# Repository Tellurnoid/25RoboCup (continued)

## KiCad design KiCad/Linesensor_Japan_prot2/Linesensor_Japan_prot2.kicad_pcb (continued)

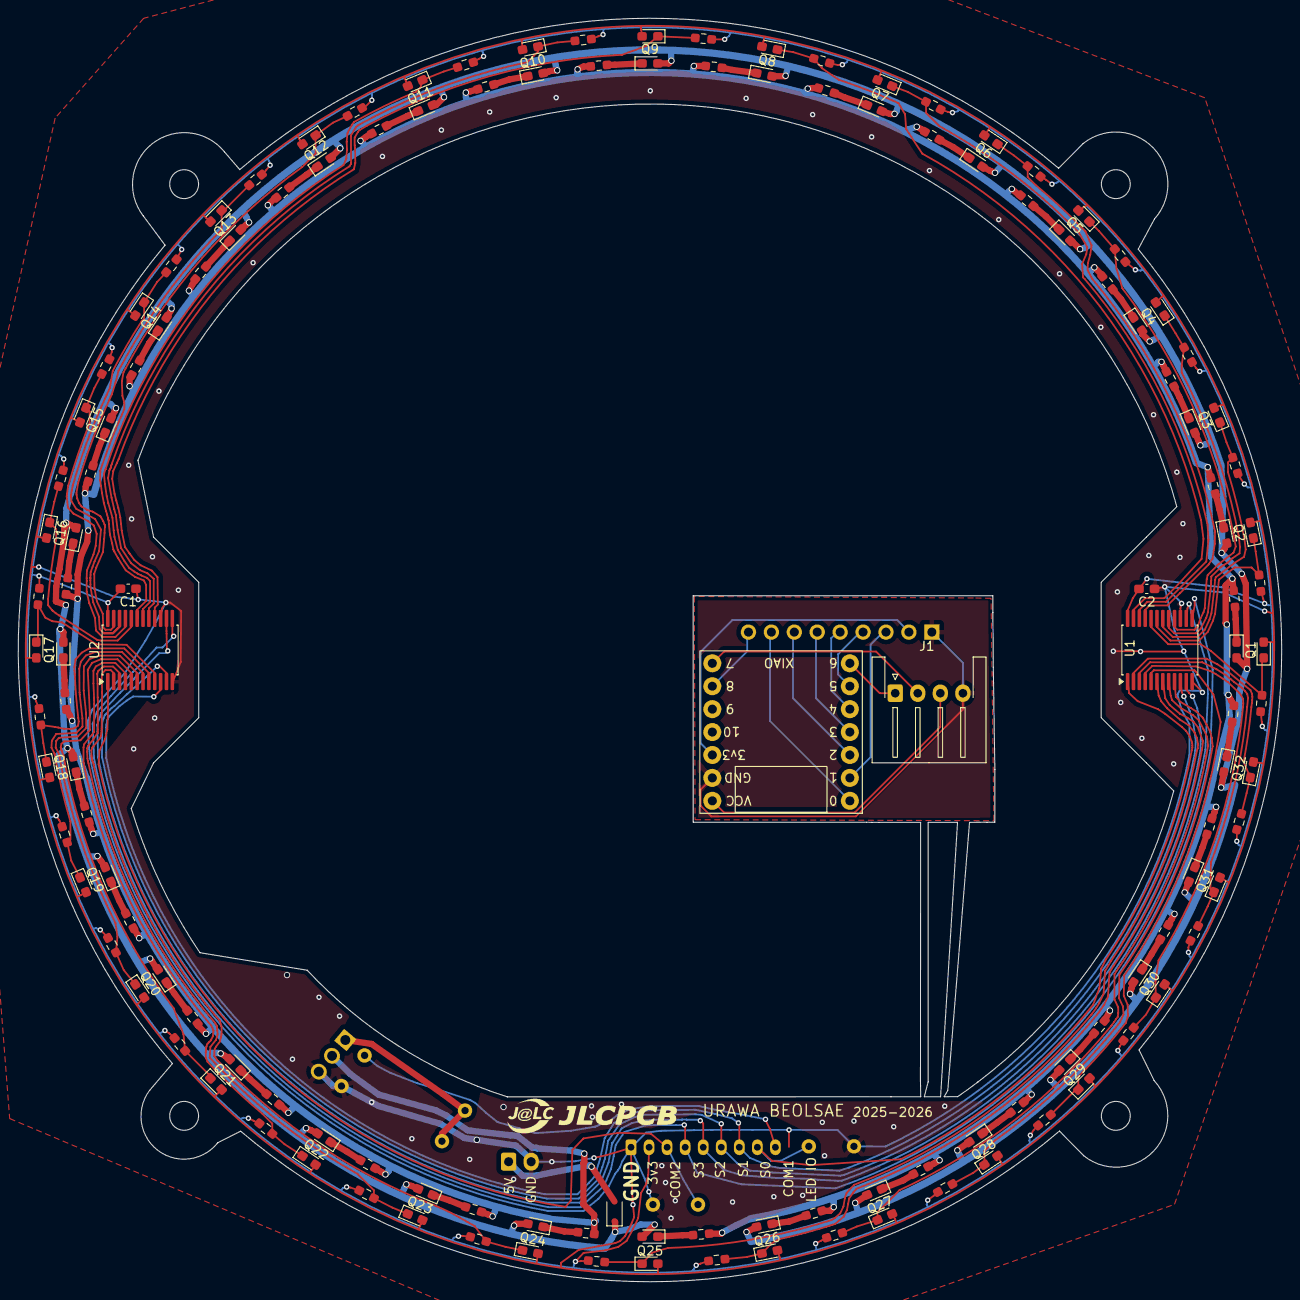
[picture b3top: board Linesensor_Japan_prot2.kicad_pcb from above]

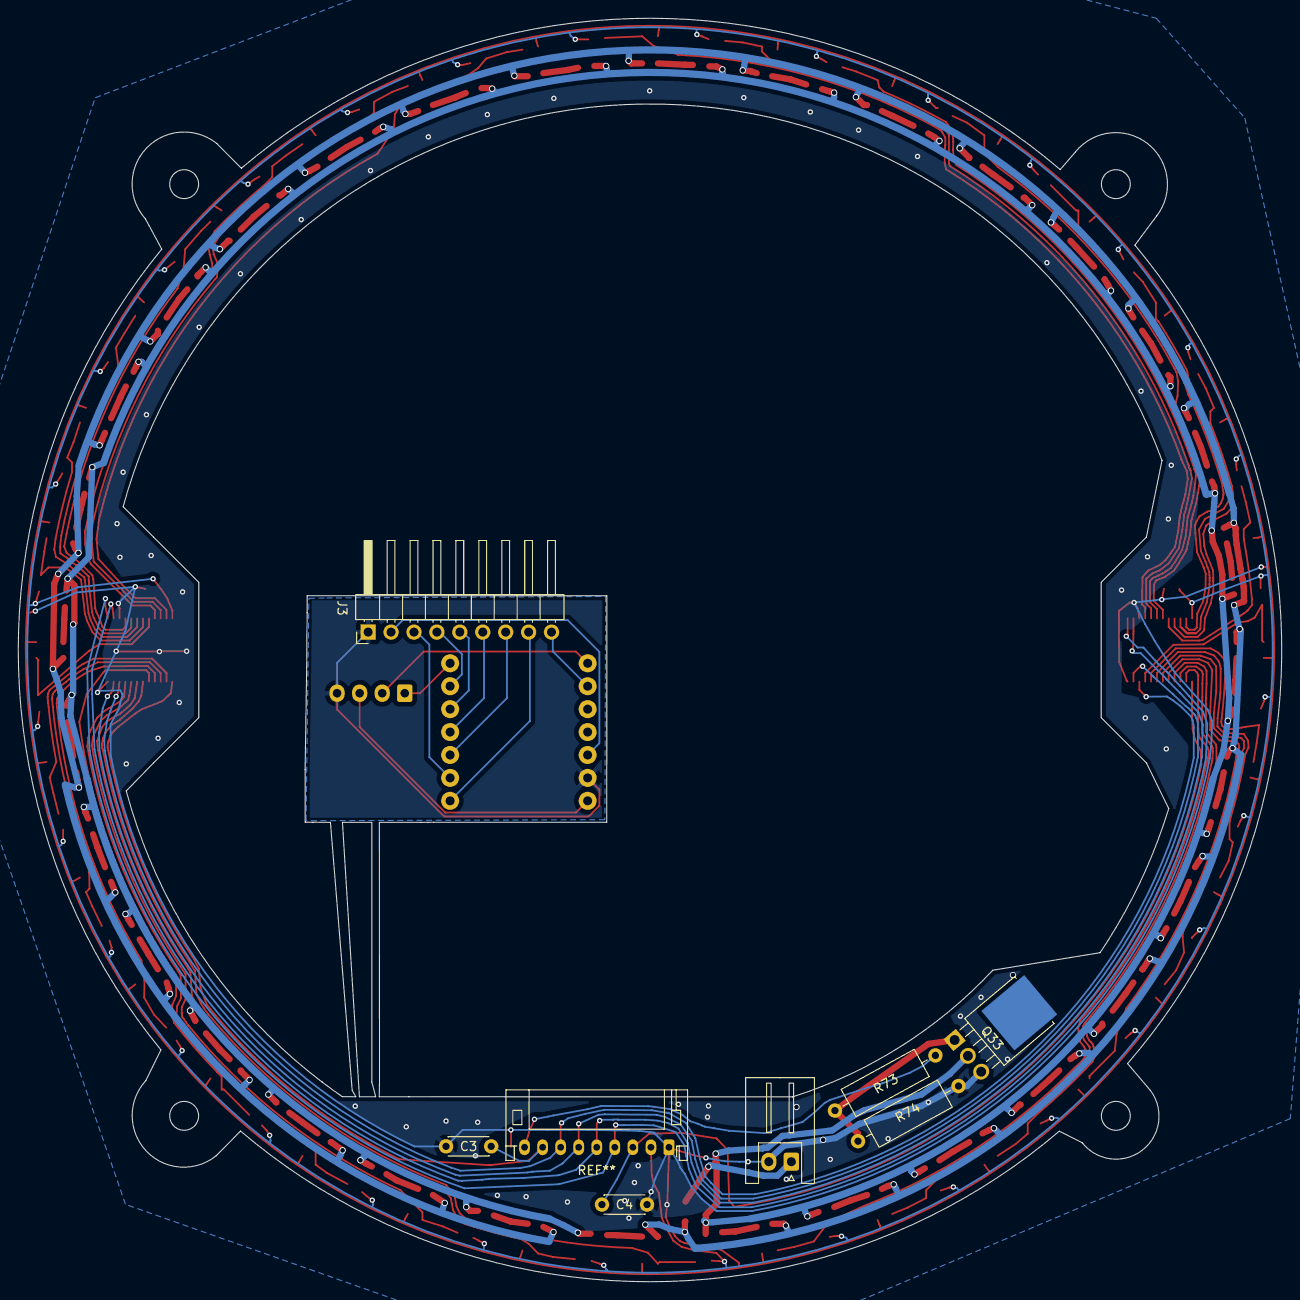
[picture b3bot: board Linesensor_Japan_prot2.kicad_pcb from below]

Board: 2 copper layers, 140.0 x 140.0 mm, 145 parts (7 on the bottom side), 79 nets.

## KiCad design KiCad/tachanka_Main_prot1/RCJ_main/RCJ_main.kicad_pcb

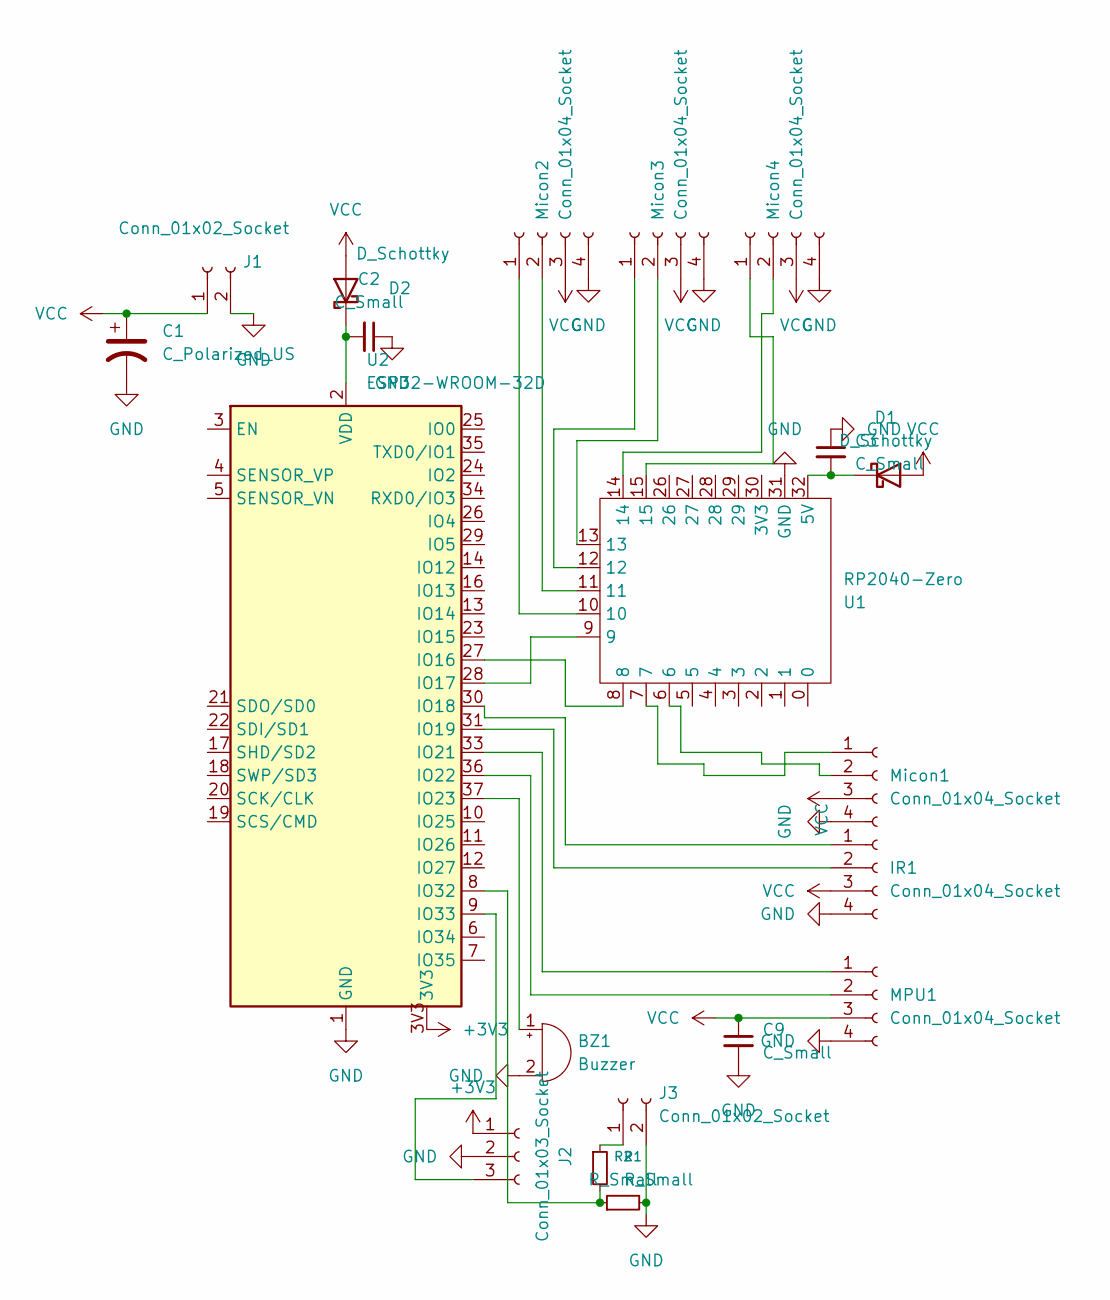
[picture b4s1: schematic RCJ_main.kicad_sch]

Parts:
BZ1: Buzzer; Buzzer_12x9.5RM7.6
C1: C_Polarized_US; CP_Radial_D8.0mm_P3.50mm
C2, C3, C9: C_Small; CP_EIA-1608-08_AVX-J_HandSolder
D1, D2: D_Schottky; D_SOD-123
IR1: Conn_01x04_Socket; JST_PH_S4B-PH-K_1x04_P2.00mm_Horizontal
J1: Conn_01x02_Socket; JST_XH_S2B-XH-A-1_1x02_P2.50mm_Horizontal
J2: Conn_01x03_Socket; JST_PH_B3B-PH-K_1x03_P2.00mm_Vertical
J3: Conn_01x02_Socket; JST_PH_B2B-PH-K_1x02_P2.00mm_Vertical
MPU1: Conn_01x04_Socket; MPU6050
Micon1, Micon2, Micon3: Conn_01x04_Socket; JST_PH_B4B-PH-K_1x04_P2.00mm_Vertical
Micon4: Conn_01x04_Socket; JST_PH_S4B-PH-K_1x04_P2.00mm_Horizontal
R1, R2: R_Small; R_Axial_DIN0207_L6.3mm_D2.5mm_P10.16mm_Horizontal
U1: RP2040-Zero; RP2040-Zero-THT
U2: ESP32-WROOM-32D; ESP32_devModule

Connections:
+3V3: J2.1, U2.3V3
GND: BZ1.2 (-), C1.2, C2.1, C3.1, C9.2, IR1.4, J1.2, J2.2, J3.2, MPU1.4, Micon1.4, Micon2.4, Micon3.4, Micon4.4, R2.2, U1.31 (GND), U2.1 (GND), U2.15 (GND), U2.38 (GND), U2.39 (GND)
unnamed: BZ1.1 (+), U2.37 (IO23)
unnamed: C3.2, D1.1 (K), U1.32 (5V)
unnamed: C2.2, D2.1 (K), U2.2 (VDD)
unnamed: IR1.1, U2.30 (IO18)
unnamed: IR1.2, U2.31 (IO19)
unnamed: J2.3, U2.9 (IO33)
unnamed: J3.1, R1.1
unnamed: MPU1.1, U2.33 (IO21)
unnamed: MPU1.2, U2.36 (IO22)
unnamed: Micon1.1, U1.7
unnamed: Micon1.2, U1.6
unnamed: Micon2.1, U1.10
unnamed: Micon2.2, U1.11
unnamed: Micon3.1, U1.12
unnamed: Micon3.2, U1.13
unnamed: Micon4.1, U1.15
unnamed: Micon4.2, U1.14
unnamed: U1.8, U2.27 (IO16)
unnamed: U1.9, U2.28 (IO17)
unnamed: R1.2, R2.1, U2.8 (IO32)
VCC: C1.1, C9.1, D1.2 (A), D2.2 (A), IR1.3, J1.1, MPU1.3, Micon1.3, Micon2.3, Micon3.3, Micon4.3

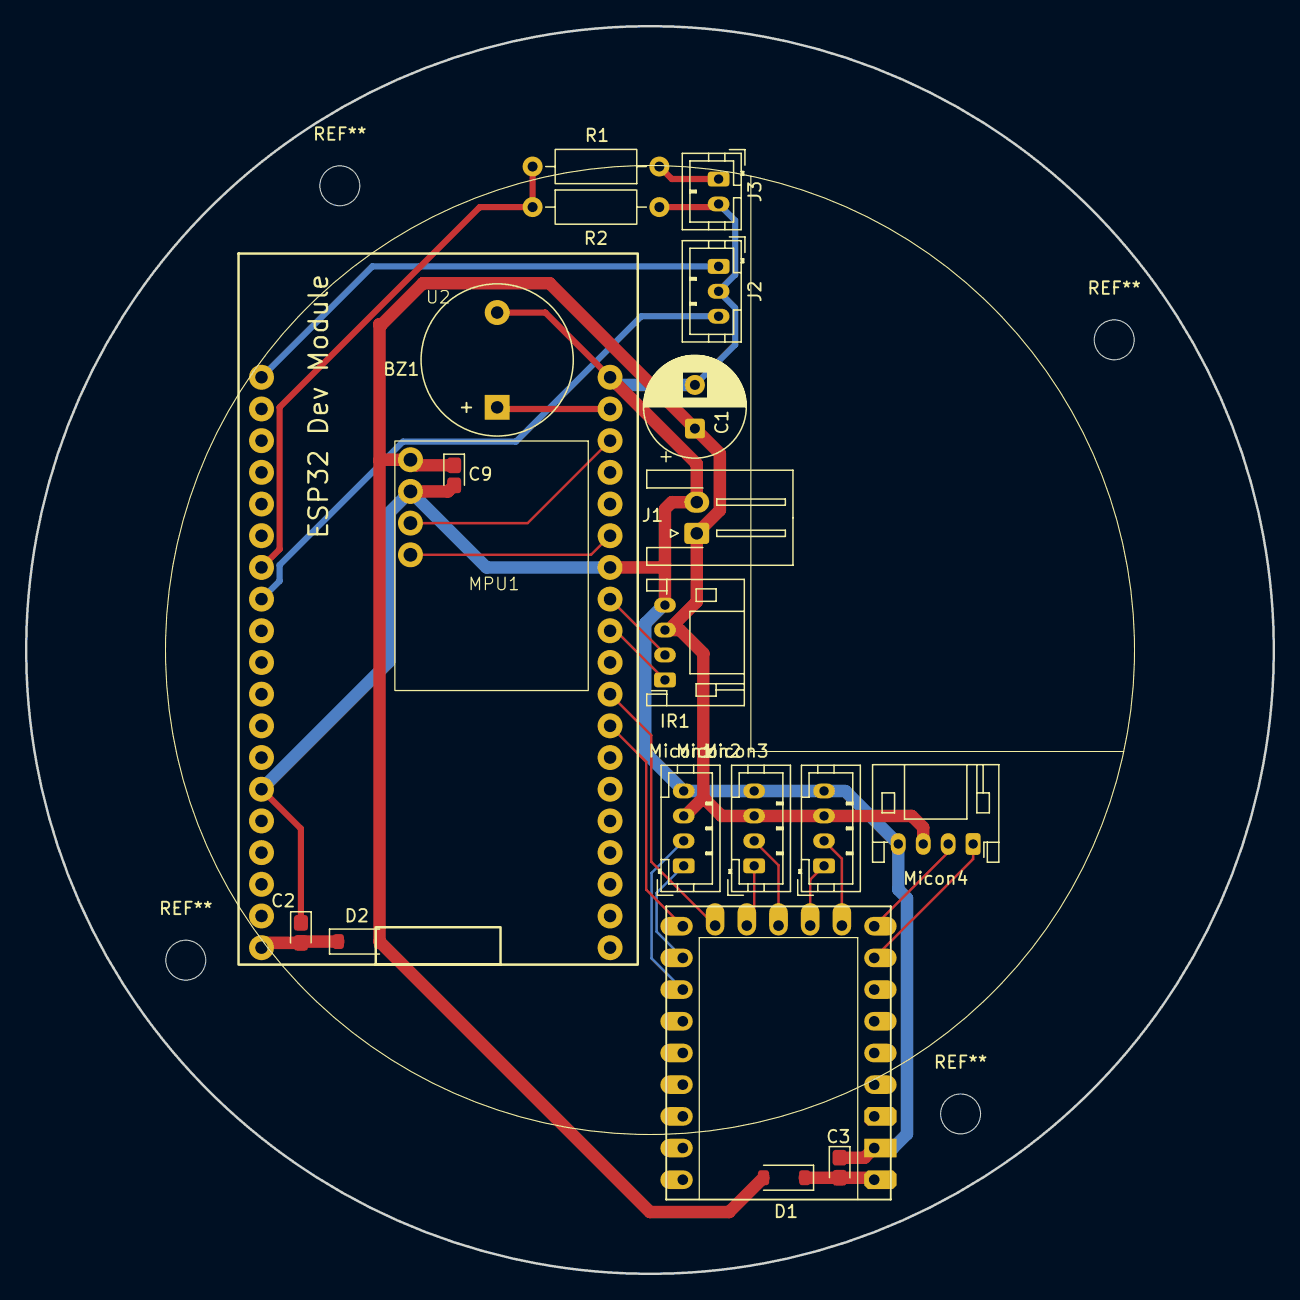
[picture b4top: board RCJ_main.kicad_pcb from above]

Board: 2 copper layers, 100.0 x 100.0 mm, 20 parts (0 on the bottom side), 23 nets.

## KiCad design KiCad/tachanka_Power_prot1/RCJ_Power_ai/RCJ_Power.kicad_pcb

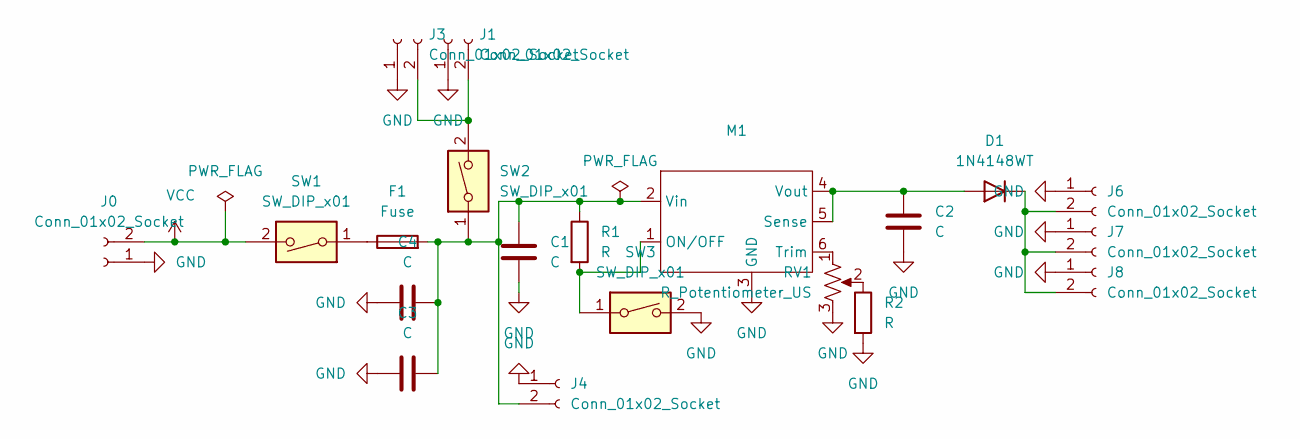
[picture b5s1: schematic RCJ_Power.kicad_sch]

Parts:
C1, C2: C; CP_EIA-1608-10_AVX-L_HandSolder
C3, C4: C; CP_Radial_D12.5mm_P5.00mm
D1: 1N4148WT; D_SMC
F1: Fuse; Fuseholder
J0: Conn_01x02_Socket; AMASS_XT60-M_1x02_P7.20mm_Vertical
J1: Conn_01x02_Socket; AMASS_XT30U-M_1x02_P5.0mm_Vertical
J3, J6, J7, J8: Conn_01x02_Socket; JST_XH_B2B-XH-A_1x02_P2.50mm_Vertical
J4: Conn_01x02_Socket; 2Connect
M1: MURATA_OKL-KAIZOU
R1: R; R_Axial_DIN0207_L6.3mm_D2.5mm_P10.16mm_Horizontal
R2: R; R_Axial_DIN0204_L3.6mm_D1.6mm_P5.08mm_Horizontal
RV1: R_Potentiometer_US; Potentiometer_Bourns_3296W_Vertical
SW1, SW2: SW_DIP_x01; DS-850
SW3: SW_DIP_x01; Toggle

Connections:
GND: C1.2, C2.2, C3.1, C4.1, J0.1, J1.1, J3.1, J4.1, J6.1, J7.1, J8.1, M1.3 (GND), R2.2, RV1.3, SW3.2
unnamed: C2.1, D1.2 (A), M1.4 (Vout), M1.5 (Sense)
unnamed: D1.1 (K), J6.2, J7.2, J8.2
unnamed: F1.1, SW1.1
unnamed: J1.2, J3.2, SW2.2
unnamed: C1.1, C3.2, C4.2, F1.2, J4.2, M1.2 (Vin), R1.1, SW2.1
unnamed: M1.1 (ON/OFF), R1.2, SW3.1
unnamed: M1.6 (Trim), RV1.1
unnamed: R2.1, RV1.2
VCC: J0.2, SW1.2

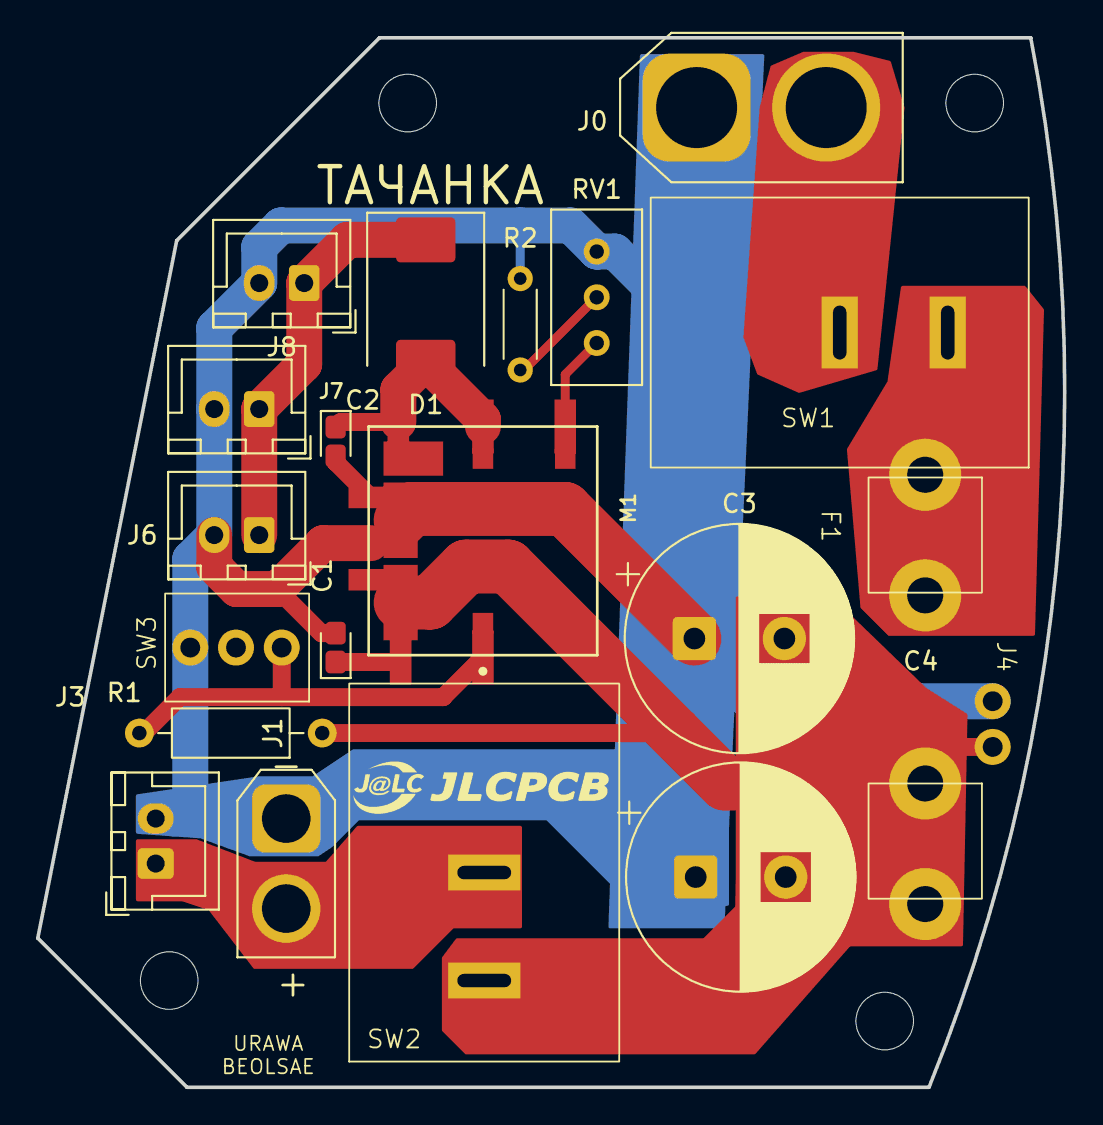
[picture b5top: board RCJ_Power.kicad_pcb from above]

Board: 2 copper layers, 57.1 x 58.3 mm, 20 parts (0 on the bottom side), 10 nets.

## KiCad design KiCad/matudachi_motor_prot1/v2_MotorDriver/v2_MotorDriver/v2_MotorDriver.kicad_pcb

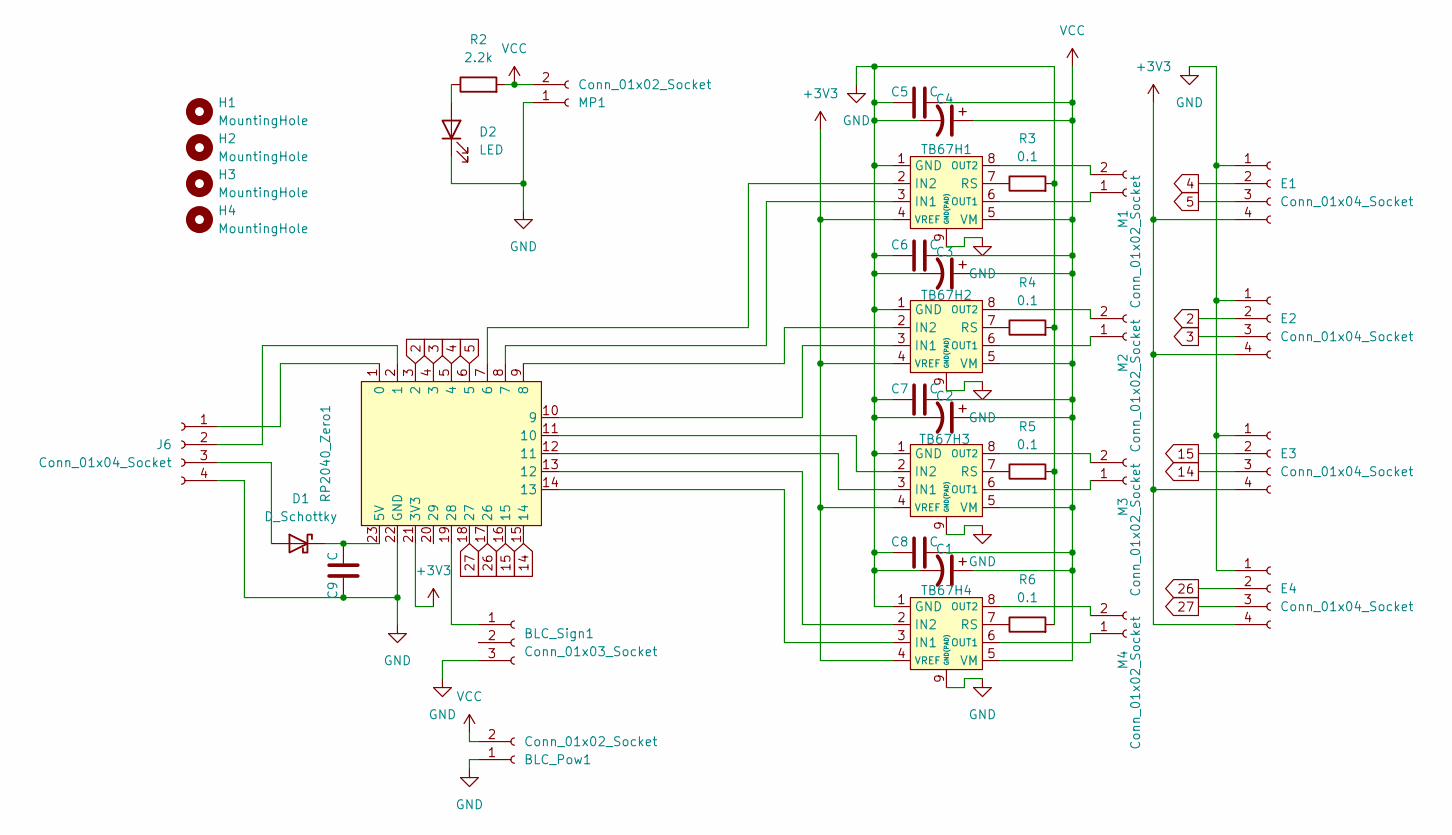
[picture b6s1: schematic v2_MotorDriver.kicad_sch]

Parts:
BLC_Pow1: Conn_01x02_Socket; AMASS_XT30U-F_1x02_P5.0mm_Vertical
BLC_Sign1: Conn_01x03_Socket; JST_XH_B3B-XH-A_1x03_P2.50mm_Vertical
C1, C2, C3, C4: C_Polarized_US; CP_Radial_D6.3mm_P2.50mm
C5, C6, C7, C8, C9: C; C_0603_1608Metric_Pad1.08x0.95mm_HandSolder
D1: D_Schottky; D_SOD-323F
D2: LED; LED_0603_1608Metric_Pad1.05x0.95mm_HandSolder
E1, E2, E3, E4: Conn_01x04_Socket; JST_PH_B4B-PH-K_1x04_P2.00mm_Vertical
H1, H2, H3, H4: MountingHole; MountingHole_3.2mm_M3
J6: Conn_01x04_Socket; JST_XH_B4B-XH-A_1x04_P2.50mm_Vertical
M1, M2, M3, M4: Conn_01x02_Socket; JST_VH_B2P-VH-B_1x02_P3.96mm_Vertical
MP1: Conn_01x02_Socket; AMASS_XT30U-M_1x02_P5.0mm_Vertical
R2: 2.2k; R_Axial_DIN0207_L6.3mm_D2.5mm_P7.62mm_Horizontal
R3, R4, R5, R6: 0.1; R_Axial_DIN0207_L6.3mm_D2.5mm_P7.62mm_Horizontal
RP2040_Zero1: 名称未設定
TB67H1, TB67H2, TB67H3, TB67H4: SOIC-8-1EP_3.9x4.9mm_P1.27mm_EP2.29x3mm_ThermalVias

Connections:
2: E2.2, RP2040_Zero1.3 (2)
3: E2.3, RP2040_Zero1.4 (3)
4: E1.2, RP2040_Zero1.5 (4)
5: E1.3, RP2040_Zero1.6 (5)
14: E3.3, RP2040_Zero1.15 (14)
15: E3.2, RP2040_Zero1.16 (15)
26: E4.2, RP2040_Zero1.17 (26)
27: E4.3, RP2040_Zero1.18 (27)
+3V3: E1.4, E2.4, E3.4, E4.4, RP2040_Zero1.21 (3V3), TB67H1.4 (VREF), TB67H2.4 (VREF), TB67H3.4 (VREF), TB67H4.4 (VREF)
GND: BLC_Pow1.1, BLC_Sign1.3, C1.2, C2.2, C3.2, C4.2, C5.1, C6.1, C7.1, C8.1, C9.1, D2.1 (K), E1.1, E2.1, E3.1, E4.1, J6.4, MP1.1, R3.2, R4.2, R5.2, R6.2, RP2040_Zero1.22 (GND), TB67H1.1 (GND), TB67H1.9 (GND(PAD)), TB67H2.1 (GND), TB67H2.9 (GND(PAD)), TB67H3.1 (GND), TB67H3.9 (GND(PAD)), TB67H4.1 (GND), TB67H4.9 (GND(PAD))
unnamed: BLC_Sign1.1, RP2040_Zero1.19 (28)
unnamed: D1.2 (A), J6.3
unnamed: C9.2, D1.1 (K), RP2040_Zero1.23 (5V)
unnamed: D2.2 (A), R2.1
unnamed: J6.1, RP2040_Zero1.1 (0)
unnamed: J6.2, RP2040_Zero1.2 (1)
unnamed: M1.1, TB67H1.6 (OUT1)
unnamed: M1.2, TB67H1.8 (OUT2)
unnamed: M2.1, TB67H2.6 (OUT1)
unnamed: M2.2, TB67H2.8 (OUT2)
unnamed: M3.1, TB67H3.6 (OUT1)
unnamed: M3.2, TB67H3.8 (OUT2)
unnamed: M4.1, TB67H4.6 (OUT1)
unnamed: M4.2, TB67H4.8 (OUT2)
unnamed: RP2040_Zero1.7 (6), TB67H1.2 (IN2)
unnamed: RP2040_Zero1., RP2040_Zero1.8 (7), TB67H1.3 (IN1)
unnamed: RP2040_Zero1.9 (8), TB67H2.2 (IN2)
unnamed: RP2040_Zero1.10 (9), TB67H2.3 (IN1)
unnamed: RP2040_Zero1.11 (10), TB67H3.2 (IN2)
unnamed: RP2040_Zero1.12 (11), TB67H3.3 (IN1)
unnamed: RP2040_Zero1.13 (12), TB67H4.2 (IN2)
unnamed: RP2040_Zero1.14 (13), TB67H4.3 (IN1)
unnamed: R3.1, TB67H1.7 (RS)
unnamed: R4.1, TB67H2.7 (RS)
unnamed: R5.1, TB67H3.7 (RS)
unnamed: R6.1, TB67H4.7 (RS)
VCC: BLC_Pow1.2, C1.1, C2.1, C3.1, C4.1, C5.2, C6.2, C7.2, C8.2, MP1.2, R2.2, TB67H1.5 (VM), TB67H2.5 (VM), TB67H3.5 (VM), TB67H4.5 (VM)

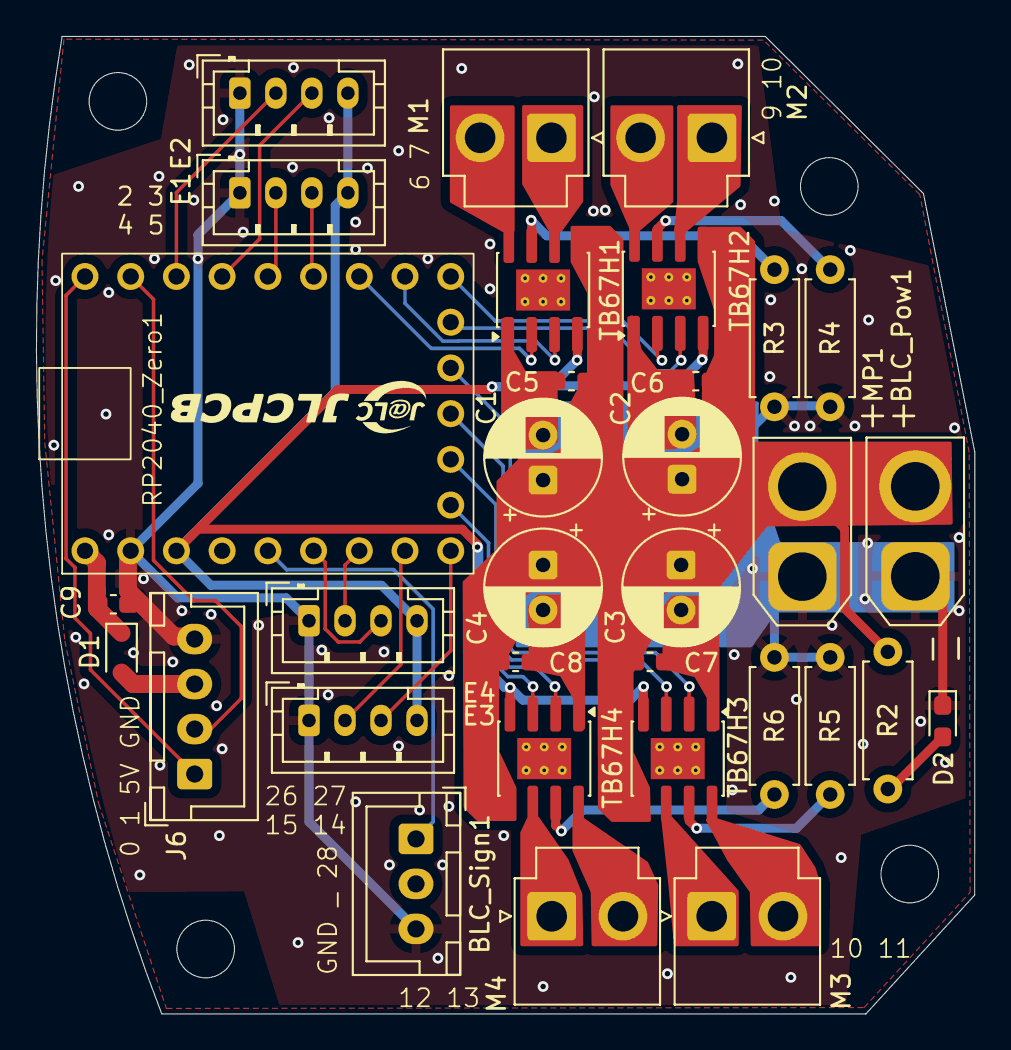
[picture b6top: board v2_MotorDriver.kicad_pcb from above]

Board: 2 copper layers, 52.1 x 54.3 mm, 37 parts (0 on the bottom side), 37 nets.

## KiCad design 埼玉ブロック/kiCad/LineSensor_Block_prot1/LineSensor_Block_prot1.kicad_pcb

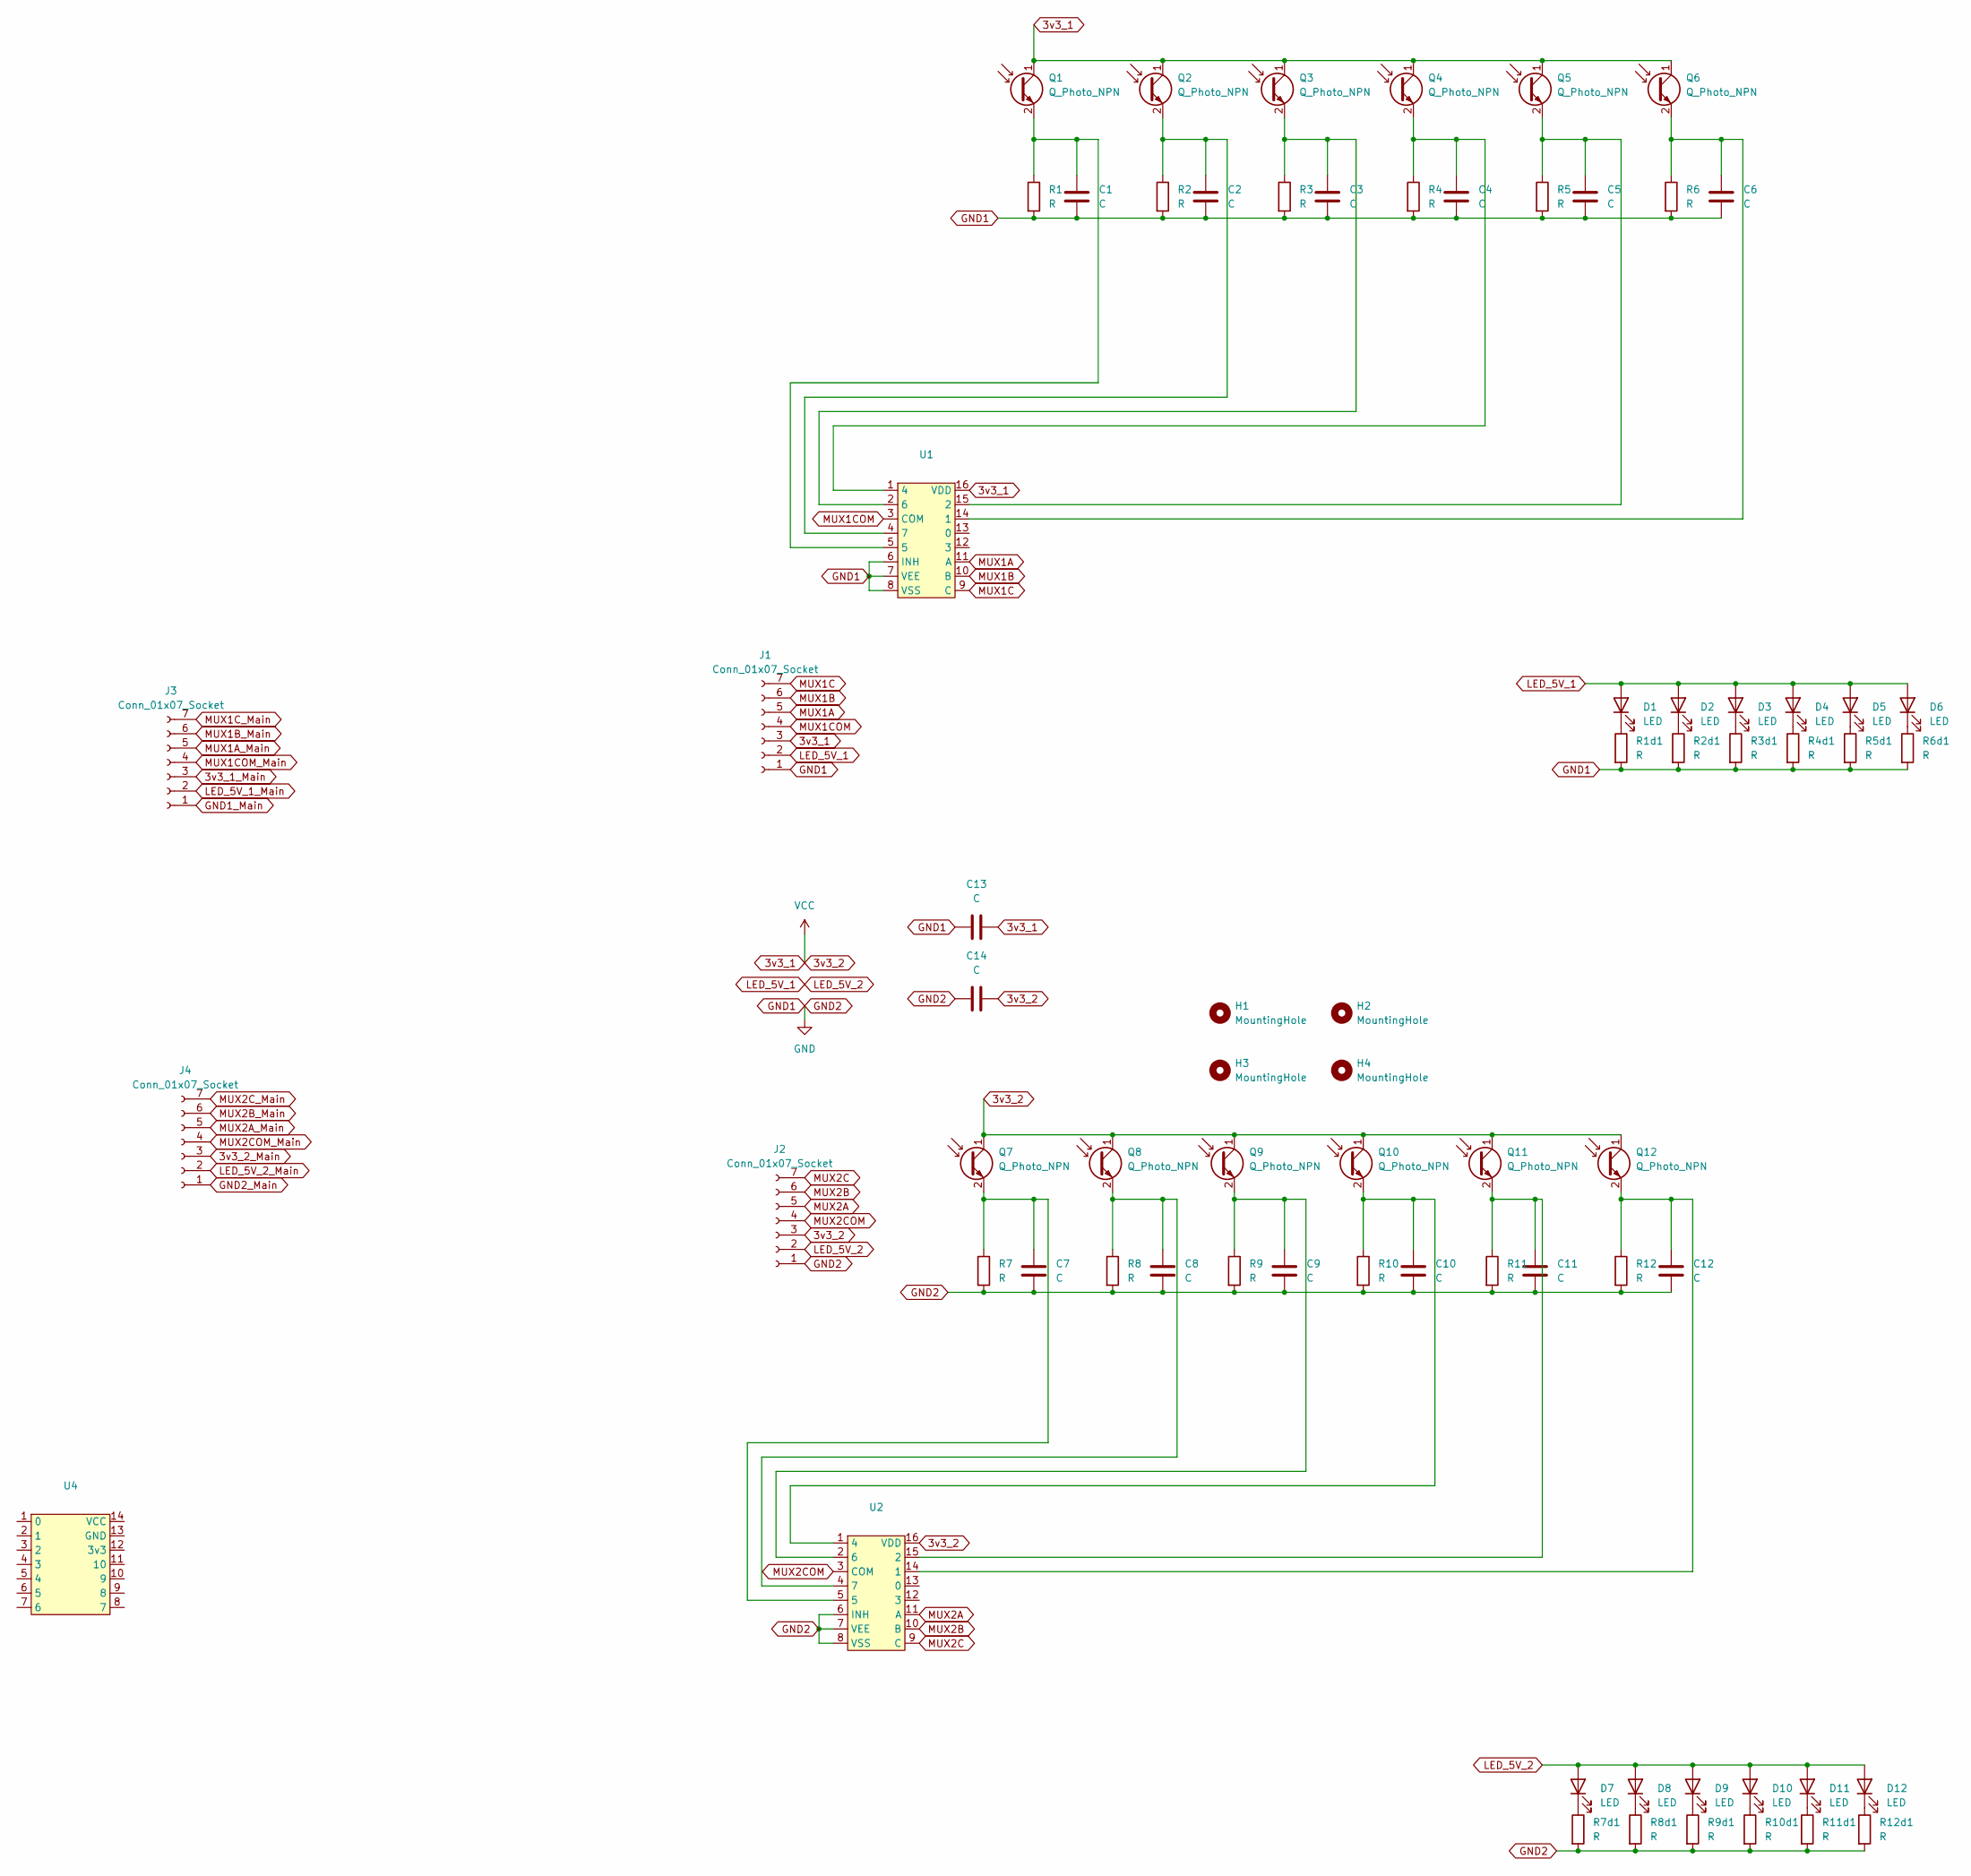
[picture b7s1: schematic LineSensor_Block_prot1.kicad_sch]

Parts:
C1, C2, C3, C4, C5, C6, C8, C9, C10, C11, C12, C13, C14: C; C_0603_1608Metric
C7: C; R_0603_1608Metric
D1, D2, D3, D4, D5, D6, D7, D8, D9, D10, D11, D12: LED; LED_0603_1608Metric
H1, H2, H3, H4: MountingHole; MountingHole_3.2mm_M3
J1, J2: Conn_01x07_Socket; PinHeader_1x07_P2.54mm_Horizontal_edited
J3, J4: Conn_01x07_Socket; PinSocket_1x07_P2.54mm_Horizontal_edited
Q1, Q2, Q3, Q4, Q5, Q6, Q7, Q8, Q9, Q10, Q11, Q12: Q_Photo_NPN; LED_0603_1608Metric
R1, R1d1, R2, R2d1, R3, R3d1, R4, R4d1, R5, R5d1, R6, R6d1, R7, R7d1, R8, R8d1, R9, R9d1, R10, R10d1, R11, R11d1, R12, R12d1: R; R_0603_1608Metric
U1, U2: TSSOP-16_4.4x5mm_P0.65mm
U4: 名称未設定

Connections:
3v3_1: C13.2, C14.2, J1.3, J2.3, Q1.1 (C), Q2.1 (C), Q3.1 (C), Q4.1 (C), Q5.1 (C), Q6.1 (C), Q7.1 (C), Q8.1 (C), Q9.1 (C), Q10.1 (C), Q11.1 (C), Q12.1 (C), U1.16 (VDD), U2.16 (VDD)
3v3_1_Main: J3.3
3v3_2_Main: J4.3
GND1: C1.2, C2.2, C3.2, C4.2, C5.2, C6.2, C7.2, C8.2, C9.2, C10.2, C11.2, C12.2, C13.1, C14.1, J1.1, J2.1, R1.2, R1d1.2, R2.2, R2d1.2, R3.2, R3d1.2, R4.2, R4d1.2, R5.2, R5d1.2, R6.2, R6d1.2, R7.2, R7d1.2, R8.2, R8d1.2, R9.2, R9d1.2, R10.2, R10d1.2, R11.2, R11d1.2, R12.2, R12d1.2, U1.6 (INH), U1.7 (VEE), U1.8 (VSS), U2.6 (INH), U2.7 (VEE), U2.8 (VSS)
GND1_Main: J3.1
GND2_Main: J4.1
LED_5V_1: D1.2 (A), D2.2 (A), D3.2 (A), D4.2 (A), D5.2 (A), D6.2 (A), D7.2 (A), D8.2 (A), D9.2 (A), D10.2 (A), D11.2 (A), D12.2 (A), J1.2, J2.2
LED_5V_1_Main: J3.2
LED_5V_2_Main: J4.2
MUX1A: J1.5, U1.11 (A)
MUX1A_Main: J3.5
MUX1B: J1.6, U1.10 (B)
MUX1B_Main: J3.6
MUX1C: J1.7, U1.9 (C)
MUX1COM: J1.4, U1.3 (COM)
MUX1COM_Main: J3.4
MUX1C_Main: J3.7
MUX2A: J2.5, U2.11 (A)
MUX2A_Main: J4.5
MUX2B: J2.6, U2.10 (B)
MUX2B_Main: J4.6
MUX2C: J2.7, U2.9 (C)
MUX2COM: J2.4, U2.3 (COM)
MUX2COM_Main: J4.4
MUX2C_Main: J4.7
unnamed: D1.1 (K), R1d1.1
unnamed: D2.1 (K), R2d1.1
unnamed: D3.1 (K), R3d1.1
unnamed: D4.1 (K), R4d1.1
unnamed: D5.1 (K), R5d1.1
unnamed: D6.1 (K), R6d1.1
unnamed: D7.1 (K), R7d1.1
unnamed: D8.1 (K), R8d1.1
unnamed: D9.1 (K), R9d1.1
unnamed: D10.1 (K), R10d1.1
unnamed: D11.1 (K), R11d1.1
unnamed: D12.1 (K), R12d1.1
unnamed: C1.1, Q1.2 (E), R1.1, U1.5
unnamed: C2.1, Q2.2 (E), R2.1, U1.4 (7)
unnamed: C3.1, Q3.2 (E), R3.1, U1.2 (6)
unnamed: C4.1, Q4.2 (E), R4.1, U1.1 (4)
unnamed: C5.1, Q5.2 (E), R5.1, U1.15 (2)
unnamed: C6.1, Q6.2 (E), R6.1, U1.14 (1)
unnamed: C7.1, Q7.2 (E), R7.1, U2.5
unnamed: C8.1, Q8.2 (E), R8.1, U2.4 (7)
unnamed: C9.1, Q9.2 (E), R9.1, U2.2 (6)
unnamed: C10.1, Q10.2 (E), R10.1, U2.1 (4)
unnamed: C11.1, Q11.2 (E), R11.1, U2.15 (2)
unnamed: C12.1, Q12.2 (E), R12.1, U2.14 (1)

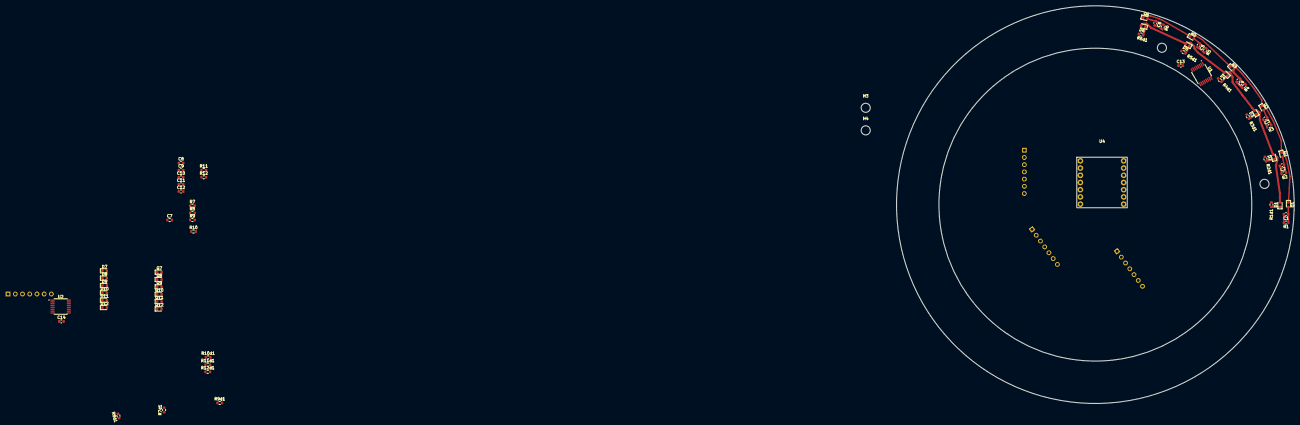
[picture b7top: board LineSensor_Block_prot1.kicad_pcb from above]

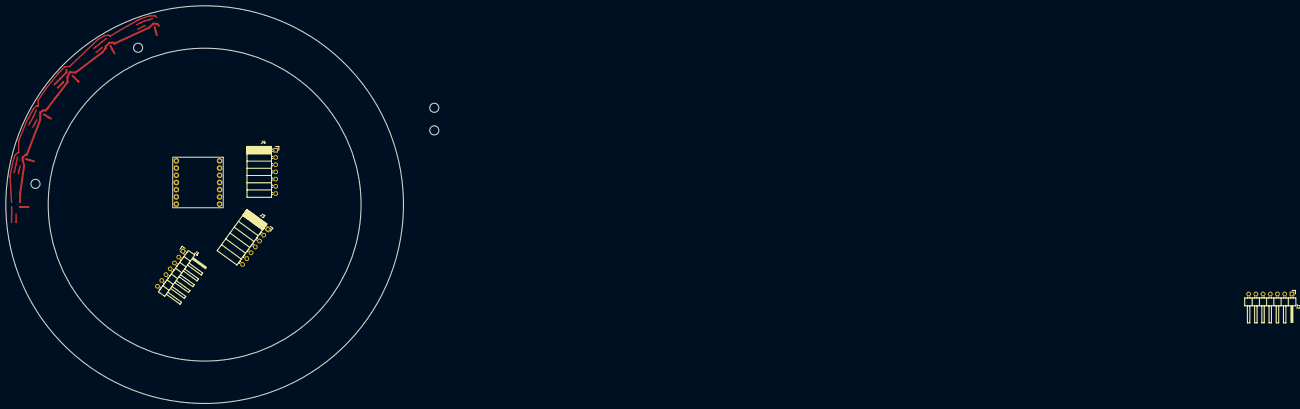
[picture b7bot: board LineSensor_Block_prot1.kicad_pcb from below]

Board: 2 copper layers, 140.0 x 140.0 mm, 73 parts (4 on the bottom side), 35 nets.

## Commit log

2025-10-04 readme
2025-10-06 10.6 kicad追加
2025-10-06 10.6 kicad追加2
2025-10-25 カメラの青色検出のテストコード.25.9.25
2025-10-25 すこしラインセンサーの回路を進めた.25.9.25
2025-10-26 withYata.9.26
2025-10-26 withYata.9.26(＋ファイル整理)
2025-10-26 withYata.9.26(＋コメント整理)
2025-10-26 ロゴ追加
2025-11-03 フットプリント割あて.25.11.3
2025-11-04 外形の図形10.5
2025-11-08 kicadのprot3作ってフットプリントwith桑子.11.8
2025-11-09 円とセンサーの配置ずれるな..11/9
2025-11-09 センサーフットプリント調整.11.9
2025-11-11 修学旅行行き新幹線
2025-11-11 11/1夜_LED配置まで
2025-11-13 企画別行き
2025-11-13 LM393円形1
2025-11-15 円形最低限
2025-11-15 25.11.15
2025-11-17 円形配置 抵抗を平行に
2025-11-19 prot4作成
2025-11-19 prot4のdrc警告なし
2025-11-19 11/19バケモンスケジュール
2025-11-22 配置変更1
2025-11-23 11.24朝desktop
2025-11-24 11.24桑子チェック1
2025-11-24 完成？(GPIO照らし合わせ)
2025-11-24 完成？(月曜帰宅)
2025-11-25 11.25チーム名印字など
2025-11-25 ガーバー作成1
2025-11-26 ssd1306UIスケッチファイル作成
2025-11-26 UI基板カーソル完成
2025-11-27 ガーバー再アップロード
2025-11-28 モタドラ趣味開始
2025-11-29 EEPROM試験完了
2025-11-29 UI基板基礎関数完成
2025-12-01 UI基板フォント調整まで完成
2025-12-01 boolセットアプリ実装
2025-12-03 prot2作成
2025-12-03 12.3
2025-12-03 prot2基本関数配置
2025-12-04 ラインセンサーlm393短足
2025-12-05 12.5バスケ行く前
2025-12-08 12.8
2025-12-11 UI基板シリアルのみ完成
2025-12-12 金曜バッテリーなし
2025-12-12 たつきのコード
2025-12-12 12.12帰る前
2025-12-14 北埼玉ノード終了
2025-12-16 esc最初の実験
2025-12-17 ラインセンサー部品ほぼ決定
2025-12-17 注文書消した
2025-12-18 ラインセンサー素子部回路配置まで、IC割当トラブル中
2025-12-19 ラインセンサー外側の配置と配線
2025-12-22 マルチプレクソ16chにするくそ
2025-12-23 ラインセンサー再配置開始
2025-12-25 24夜まで
2025-12-25 マルツ行く前
2025-12-25 あきはばら
2025-12-25 マイコン基板円形わお
2025-12-26 kicad欄センサーエラー0まで
2025-12-26 marudachi
2025-12-26 ガーバー作成後1
2025-12-26 PCB3基板発注後
2025-12-28 ふぉるだ
2025-12-28 あ.txt
2025-12-28 キーパーソフト開始
2025-12-30 rp2040PIO試験成功、キーパー機全角度対応開始
2025-12-31 とち狂い極座標を使用開始
2026-01-01 打ち消しプログラム仮完成、動作確認はまだ
2026-01-01 キーパーソフト基礎完成、超音波なし
2026-01-02 ラインセンサー基本読み込みコード完成、UARTとキャリブレーションはまだ
2026-01-06 スキー帰り
2026-01-07 rp2040メイン基板シリアル問題解消
2026-01-08 UI基板ライブラリ依存関係問題解消
2026-01-08 UIと通信開発
2026-01-08 ラインセンサーlm393はずれてくそ
2026-01-09 ラインセンサー復活！？
2026-01-09 超音波少し実装、カメラやれ
2026-01-24 雑用ファイル追加fromDesktop
2026-01-29 鬼円形配置爆完了
2026-01-30 ラインセンサーprot1ほぼ完成
2026-01-31 prot2ほぼ完成
2026-02-01 ああああああああああああああああああ
2026-02-03 IR配置ほぼ完了
2026-02-03 すこしひらいた
2026-02-04 IR配線仕上げ前
2026-02-04 IR完成
2026-02-05 IRあと文字
2026-02-05 IRシルク書き込みまで完成
2026-02-06 IRmadeowari
2026-02-07 ラインセンサーベタ削除
2026-02-08 キーパー触れ始め
2026-02-09 IRのXH4修正、発注
2026-02-10 パーカー注文
2026-02-11 sakuaku
2026-02-14 リンクページ完成
2026-02-15 HP，CAD設計担当修正
2026-02-15 ライントレース7割
2026-02-16 カメラ通信成功
2026-02-16 かめらくど
2026-02-17 ラインセンサーSMDはんだ付け完了1
2026-02-18 センサーCH対応書いた
2026-02-18 打ち消し未完成
2026-02-21 ラインセンサーIRセンサーハード完成
2026-02-23 EXPO出発前
2026-02-23 EXPO後
2026-02-25 新構文キーパーソフト開始
2026-02-27 MPU動作確認
2026-02-28 新メイン仮配置完了
2026-03-01 新メイン完成
2026-03-02 ハードやないかい
2026-03-03 ポスターぎりちこ
2026-03-04 マルツ秋月大量発注
2026-03-04 画像インポートクラッシュくそ
2026-03-05 キックボードメインに結合
2026-03-05 vscode不穏な復帰
2026-03-06 すこしキーパー
2026-03-07 明日はラインセンサー簡易キャリブレーション
2026-03-08 テスト前日
2026-03-09 コンパイルエラー治らず
2026-03-10 UI基礎完成
2026-03-11 UIフォント追加まで
2026-03-14 [悲報]103と101間違える
2026-03-15 最低限ドッキング成功
2026-03-16 T字対策
2026-03-18 UI in_view関数削除
2026-03-18 UIカメラ仮実装
2026-03-20 leaveV()追加
2026-03-21 おしりトレースなし！ selfTrace完成
2026-03-22 復帰まだ不安定
2026-03-23 ボール速度実装まで
2026-03-24 キーパーダッシュ最低限実装
2026-03-25 川高帰宅前
2026-03-27 コマンドまで実装
2026-04-06 大会終了
